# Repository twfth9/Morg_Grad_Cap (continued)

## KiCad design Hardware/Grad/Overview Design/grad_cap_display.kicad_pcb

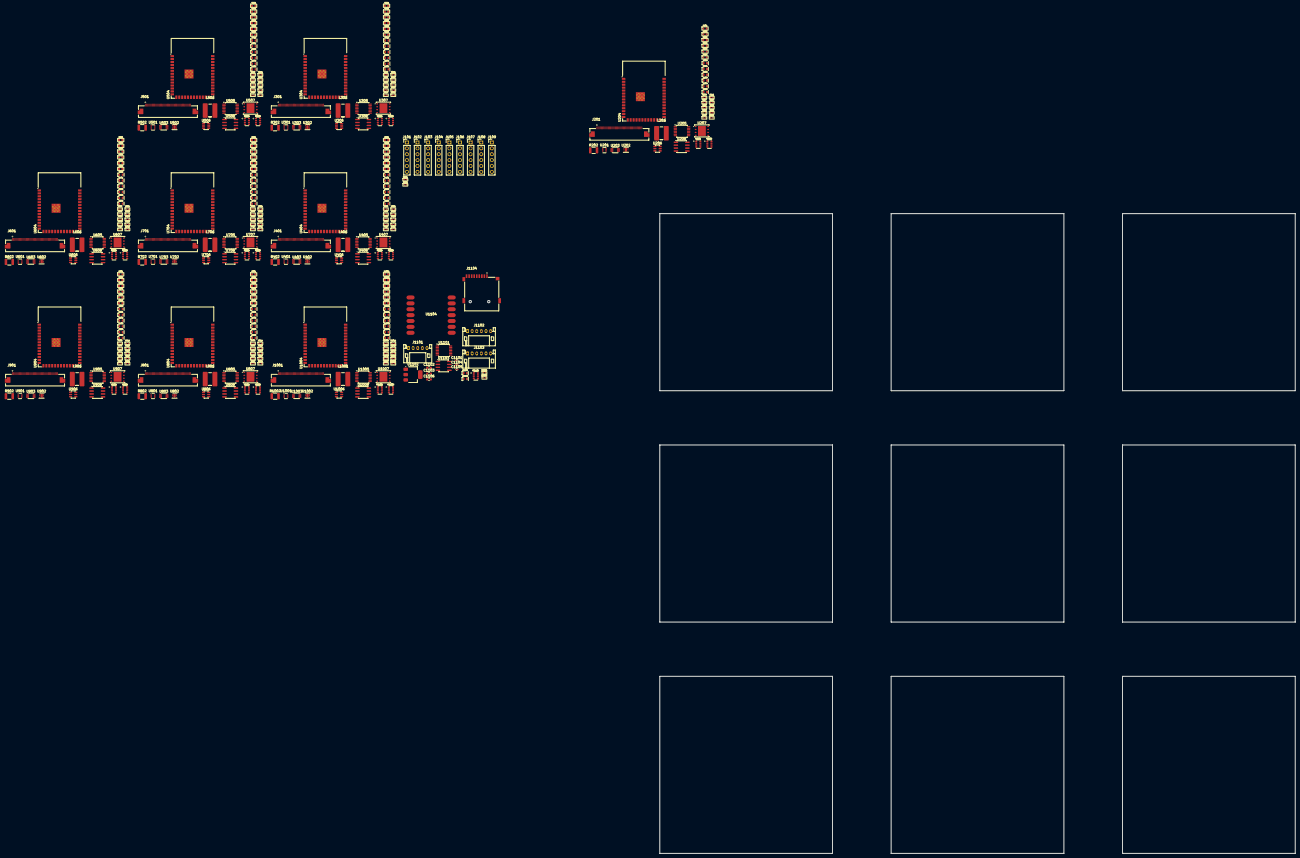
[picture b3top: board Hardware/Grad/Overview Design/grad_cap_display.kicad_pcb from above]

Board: 2 copper layers, 274.7 x 276.5 mm, 345 parts (0 on the bottom side), 444 nets, no tracks yet.

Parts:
C201, C203, C301, C303, C401, C403, C501, C503, C601, C603, C701, C703, C801, C803, C901, C903, C1001, C1003: 1uF; Worthington_C_0603
C202, C204, C206, C215, C302, C304, C306, C315, C402, C404, C406, C415, C502, C504, C506, C515, C602, C604, C606, C615, C702, C704, C706, C715, C802, C804, C806, C815, C902, C904, C906, C915, C1002, C1004, C1006, C1015: 22uF; Worthington_C_0603
C205, C207, C208, C209, C210, C211, C213, C214, C216, C305, C307, C308, C309, C310, C311, C313, C314, C316, C405, C407, C408, C409, C410, C411, C413, C414, C416, C505, C507, C508, C509, C510, C511, C513, C514, C516, C605, C607, C608, C609, C610, C611, C613, C614, C616, C705, C707, C708, C709, C710, C711, C713, C714, C716, C805, C807, C808, C809, C810, C811, C813, C814, C816, C905, C907, C908, C909, C910, C911, C913, C914, C916, C1005, C1007, C1008, C1009, C1010, C1011, C1013, C1014, C1016: 100nF; Worthington_C_0402
C212, C312, C412, C512, C612, C712, C812, C912, C1012: 22uF; Worthington_D_0603
C1101, C1104, C1105: 100nF; C_0402_1005Metric
C1102, C1103, C1106: 22uF; C_0603_1608Metric
D201, D301, D401, D501, D601, D701, D801, D901, D1001, D1101, D1102: LED_Small; Worthington_LED_0603
D202, D203, D204, D205, D302, D303, D304, D305, D402, D403, D404, D405, D502, D503, D504, D505, D602, D603, D604, D605, D702, D703, D704, D705, D802, D803, D804, D805, D902, D903, D904, D905, D1002, D1003, D1004, D1005: RED; Worthington_LED_0603
J101, J102, J103, J104, J105, J106, J107, J108, J109: 6-Pos 2.54mm Header; PinHeader_1x06_P2.54mm_Vertical
J201, J301, J401, J501, J601, J701, J801, J901, J1001: Amphenol 40-Pin FPC; AMPHENOL_62684-402100ALF
J1101: JST-PH SPI; JST_PH_S5B-PH-K_1x05_P2.00mm_Horizontal
J1102: JST-PH UART/I2C; JST_PH_S6B-PH-K_1x06_P2.00mm_Horizontal
J1103: JST-PH A#; JST_PH_S6B-PH-K_1x06_P2.00mm_Horizontal
J1104: Micro_SD_Card; CUI_MSD-4-A
L201, L301, L401, L501, L601, L701, L801, L901, L1001: 22uH; CDRH5D28
R101, R102: 120; Worthington_R_0402
R201, R301, R401, R501, R601, R701, R801, R901, R1001, R1102: 430; Worthington_R_0402
R202, R302, R402, R502, R602, R702, R802, R902, R1002: 10; R_1210_3225Metric
R1101: 1k; Worthington_R_0402
RN201, RN301, RN401, RN501, RN601, RN701, RN801, RN901, RN1001: 10k; RESCAXE80P320X160X70-8N
RN202, RN302, RN402, RN502, RN602, RN702, RN802, RN902, RN1002: 430; RESCAXE80P320X160X70-8N
RN1101: 47k; RESCAXE80P320X160X70-8N
U201, U301, U401, U501, U601, U701, U801, U901, U1001: LM66200DRLR; SOT-583-8
U202, U302, U402, U502, U602, U702, U802, U902, U1002: TLV75733PDRV; WSON-6-1EP_2x2mm_P0.65mm_EP1x1.6mm
U203, U303, U403, U503, U603, U703, U803, U903, U1003: SN74LVC1G139; VSSOP-8_2.3x2mm_P0.5mm
U204, U304, U404, U504, U604, U704, U804, U904, U1004: ESP32-S3-WROOM-1-N8R8; ESP32-S3-WROOM-1
U205, U305, U405, U505, U605, U705, U805, U905, U1005, U1101: TC7MBL3126CFT; TSSOP-14_4.4x5mm_P0.65mm
U206, U306, U406, U506, U606, U706, U806, U906, U1006: AP3019AKTTR; TSOT-23-6
U207, U307, U407, U507, U607, U707, U807, U907, U1007: W25Q128JVP; WSON-8-1EP_6x5mm_P1.27mm_EP3.4x4.3mm
U208, U308, U408, U508, U608, U708, U808, U908, U1008, U1103: THVD1400D; SOIC-8_3.9x4.9mm_P1.27mm
U1102: AZ1117-5.0; SOT-223-3_TabPin2
U1104: QTPy SAMD21; Py_QT_SAMD21

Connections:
/ESP32 1/+3V3: C204.1, C205.1, C206.1, C207.1, C208.1, C209.1, C210.1, C211.1, C216.1, D201.2 (A), J201.5 (VDD), RN201.1 (4), RN201.2, RN201.3, RN201.4, U202.1 (OUT), U203.8 (VCC), U204.2 (3V3), U205.14 (VCC), U207.8 (VCC), U208.8 (VCC)
/ESP32 1/BATT_IN: C202.1, L201.1, U201.3 (VIN1), U206.1 (SW)
/ESP32 1/LCD_RGB_DB0: J201.16 (DB0), U204.38 (IO2)
/ESP32 1/LCD_RGB_DB1: J201.17 (DB1), U204.4 (IO4)
/ESP32 1/LCD_RGB_DB2: J201.18 (DB2), U204.5 (IO5)
/ESP32 1/LCD_RGB_DB3: J201.19 (DB3), U204.6 (IO6)
/ESP32 1/LCD_RGB_DB4: J201.20 (DB4), U204.7 (IO7)
/ESP32 1/LCD_RGB_DB5: J201.21 (DB5), U204.21 (IO13)
/ESP32 1/LCD_RGB_DB6: J201.22 (DB6), U204.22 (IO14)
/ESP32 1/LCD_RGB_DB7: J201.23 (DB7), U204.8 (IO15)
/ESP32 1/LCD_RGB_DB8: J201.24 (DB8), U204.9 (IO16)
/ESP32 1/LCD_RGB_DB9: J201.25 (DB9), U204.10 (IO17)
/ESP32 1/LCD_RGB_DB10: J201.26 (DB10), U204.11 (IO18)
/ESP32 1/LCD_RGB_DB11: J201.27 (DB11), U204.13 (USB_D-)
/ESP32 1/LCD_RGB_DB12: J201.28 (DB12), U204.14 (USB_D+)
/ESP32 1/LCD_RGB_DB13: J201.29 (DB13), U204.35 (IO42)
/ESP32 1/LCD_RGB_DB14: J201.30 (DB14), U204.24 (IO47)
/ESP32 1/LCD_RGB_DB15: J201.31 (DB15), U204.25 (IO48)
/ESP32 1/LCD_RGB_DE: J201.13 (DE), U204.34 (IO41)
/ESP32 1/LCD_RGB_HSYNC: J201.15 (HS), U204.32 (IO39)
/ESP32 1/LCD_RGB_PCLK: J201.12 (PCLK), U204.31 (IO38)
/ESP32 1/LCD_RGB_VSYNC: J201.14 (VS), U204.33 (IO40)
/ESP32 1/PWR_IN: C203.1, U201.2 (VOUT), U201.7 (VOUT), U202.4 (EN), U202.6 (IN)
/ESP32 1/SPI_CS0: U203.1 (A), U204.18 (IO10)
/ESP32 1/SPI_CS1: U203.2 (B), U204.16 (IO46)
/ESP32 1/SPI_CS_FLASH: D204.2 (A), RN201.6, U203.6 (Y1), U207.1 (~CS)
/ESP32 1/SPI_CS_LCD: D205.2 (A), J201.11 (CS), RN201.5, U203.7 (Y0)
/ESP32 1/SPI_CS_µSD: D203.2 (A), D303.2 (A), D403.2 (A), D503.2 (A), D603.2 (A), D703.2 (A), D803.2 (A), D903.2 (A), D1003.2 (A), J1103.3, J1104.2 (DAT3/CD), RN201.7 (5), RN301.7 (5), RN401.7 (5), RN501.7 (5), RN601.7 (5), RN701.7 (5), RN801.7 (5), RN901.7 (5), RN1001.7 (5), RN1101.5, U203.5 (Y2), U205.11 (B4), U205.12 (A4), U303.5 (Y2), U305.11 (B4), U305.12 (A4), U403.5 (Y2), U405.11 (B4), U405.12 (A4), U503.5 (Y2), U505.11 (B4), U505.12 (A4), U603.5 (Y2), U605.11 (B4), U605.12 (A4), U703.5 (Y2), U705.11 (B4), U705.12 (A4), U803.5 (Y2), U805.11 (B4), U805.12 (A4), U903.5 (Y2), U905.11 (B4), U905.12 (A4), U1003.5 (Y2), U1005.11 (B4), U1005.12 (A4), U1101.11 (B4), U1101.12 (A4), U1104.2 (A1)
/ESP32 1/SPI_MISO: U204.26 (IO45), U205.3 (B1), U207.2 (DO/IO_{1})
/ESP32 1/SPI_MOSI: J201.9 (SDA), U204.12 (IO8), U205.5 (A2), U207.5 (DI/IO_{0})
/ESP32 1/SPI_SCK: J201.10 (SCK), U204.17 (IO9), U205.9 (A3), U207.6 (CLK)
/ESP32 1/SPI_µSD_BUS_CONNECT: D202.2 (A), RN201.8, U203.3 (Y3), U205.1 (1~OE), U205.4 (2~OE), U205.10 (3~OE), U205.13 (4~OE)
/ESP32 1/UART-RS485_RX: U204.20 (IO12), U208.1 (RO)
/ESP32 1/UART-RS485_TX: U204.19 (IO11), U208.4 (DI)
/ESP32 1/UART_RS485_DE: U204.23 (IO21), U208.2 (~RE), U208.3 (DE)
/ESP32 2/+3V3: C304.1, C305.1, C306.1, C307.1, C308.1, C309.1, C310.1, C311.1, C316.1, D301.2 (A), J301.5 (VDD), RN301.1 (4), RN301.2, RN301.3, RN301.4, U302.1 (OUT), U303.8 (VCC), U304.2 (3V3), U305.14 (VCC), U307.8 (VCC), U308.8 (VCC)
/ESP32 2/BATT_IN: C302.1, L301.1, U301.3 (VIN1), U306.1 (SW)
/ESP32 2/LCD_RGB_DB0: J301.16 (DB0), U304.38 (IO2)
/ESP32 2/LCD_RGB_DB1: J301.17 (DB1), U304.4 (IO4)
/ESP32 2/LCD_RGB_DB2: J301.18 (DB2), U304.5 (IO5)
/ESP32 2/LCD_RGB_DB3: J301.19 (DB3), U304.6 (IO6)
/ESP32 2/LCD_RGB_DB4: J301.20 (DB4), U304.7 (IO7)
/ESP32 2/LCD_RGB_DB5: J301.21 (DB5), U304.21 (IO13)
/ESP32 2/LCD_RGB_DB6: J301.22 (DB6), U304.22 (IO14)
/ESP32 2/LCD_RGB_DB7: J301.23 (DB7), U304.8 (IO15)
/ESP32 2/LCD_RGB_DB8: J301.24 (DB8), U304.9 (IO16)
/ESP32 2/LCD_RGB_DB9: J301.25 (DB9), U304.10 (IO17)
/ESP32 2/LCD_RGB_DB10: J301.26 (DB10), U304.11 (IO18)
/ESP32 2/LCD_RGB_DB11: J301.27 (DB11), U304.13 (USB_D-)
/ESP32 2/LCD_RGB_DB12: J301.28 (DB12), U304.14 (USB_D+)
/ESP32 2/LCD_RGB_DB13: J301.29 (DB13), U304.35 (IO42)
/ESP32 2/LCD_RGB_DB14: J301.30 (DB14), U304.24 (IO47)
/ESP32 2/LCD_RGB_DB15: J301.31 (DB15), U304.25 (IO48)
/ESP32 2/LCD_RGB_DE: J301.13 (DE), U304.34 (IO41)
/ESP32 2/LCD_RGB_HSYNC: J301.15 (HS), U304.32 (IO39)
/ESP32 2/LCD_RGB_PCLK: J301.12 (PCLK), U304.31 (IO38)
/ESP32 2/LCD_RGB_VSYNC: J301.14 (VS), U304.33 (IO40)
/ESP32 2/PWR_IN: C303.1, U301.2 (VOUT), U301.7 (VOUT), U302.4 (EN), U302.6 (IN)
/ESP32 2/SPI_CS0: U303.1 (A), U304.18 (IO10)
/ESP32 2/SPI_CS1: U303.2 (B), U304.16 (IO46)
/ESP32 2/SPI_CS_FLASH: D304.2 (A), RN301.6, U303.6 (Y1), U307.1 (~CS)
/ESP32 2/SPI_CS_LCD: D305.2 (A), J301.11 (CS), RN301.5, U303.7 (Y0)
/ESP32 2/SPI_MISO: U304.26 (IO45), U305.3 (B1), U307.2 (DO/IO_{1})
/ESP32 2/SPI_MOSI: J301.9 (SDA), U304.12 (IO8), U305.5 (A2), U307.5 (DI/IO_{0})
/ESP32 2/SPI_SCK: J301.10 (SCK), U304.17 (IO9), U305.9 (A3), U307.6 (CLK)
/ESP32 2/SPI_µSD_BUS_CONNECT: D302.2 (A), RN301.8, U303.3 (Y3), U305.1 (1~OE), U305.4 (2~OE), U305.10 (3~OE), U305.13 (4~OE)
/ESP32 2/UART-RS485_RX: U304.20 (IO12), U308.1 (RO)
/ESP32 2/UART-RS485_TX: U304.19 (IO11), U308.4 (DI)
/ESP32 2/UART_RS485_DE: U304.23 (IO21), U308.2 (~RE), U308.3 (DE)
/ESP32 3/+3V3: C404.1, C405.1, C406.1, C407.1, C408.1, C409.1, C410.1, C411.1, C416.1, D401.2 (A), J401.5 (VDD), RN401.1 (4), RN401.2, RN401.3, RN401.4, U402.1 (OUT), U403.8 (VCC), U404.2 (3V3), U405.14 (VCC), U407.8 (VCC), U408.8 (VCC)
/ESP32 3/BATT_IN: C402.1, L401.1, U401.3 (VIN1), U406.1 (SW)
/ESP32 3/LCD_RGB_DB0: J401.16 (DB0), U404.38 (IO2)
/ESP32 3/LCD_RGB_DB1: J401.17 (DB1), U404.4 (IO4)
/ESP32 3/LCD_RGB_DB2: J401.18 (DB2), U404.5 (IO5)
/ESP32 3/LCD_RGB_DB3: J401.19 (DB3), U404.6 (IO6)
/ESP32 3/LCD_RGB_DB4: J401.20 (DB4), U404.7 (IO7)
/ESP32 3/LCD_RGB_DB5: J401.21 (DB5), U404.21 (IO13)
/ESP32 3/LCD_RGB_DB6: J401.22 (DB6), U404.22 (IO14)
/ESP32 3/LCD_RGB_DB7: J401.23 (DB7), U404.8 (IO15)
/ESP32 3/LCD_RGB_DB8: J401.24 (DB8), U404.9 (IO16)
/ESP32 3/LCD_RGB_DB9: J401.25 (DB9), U404.10 (IO17)
/ESP32 3/LCD_RGB_DB10: J401.26 (DB10), U404.11 (IO18)
/ESP32 3/LCD_RGB_DB11: J401.27 (DB11), U404.13 (USB_D-)
/ESP32 3/LCD_RGB_DB12: J401.28 (DB12), U404.14 (USB_D+)
/ESP32 3/LCD_RGB_DB13: J401.29 (DB13), U404.35 (IO42)
/ESP32 3/LCD_RGB_DB14: J401.30 (DB14), U404.24 (IO47)
/ESP32 3/LCD_RGB_DB15: J401.31 (DB15), U404.25 (IO48)
/ESP32 3/LCD_RGB_DE: J401.13 (DE), U404.34 (IO41)
/ESP32 3/LCD_RGB_HSYNC: J401.15 (HS), U404.32 (IO39)
/ESP32 3/LCD_RGB_PCLK: J401.12 (PCLK), U404.31 (IO38)
/ESP32 3/LCD_RGB_VSYNC: J401.14 (VS), U404.33 (IO40)
/ESP32 3/PWR_IN: C403.1, U401.2 (VOUT), U401.7 (VOUT), U402.4 (EN), U402.6 (IN)
/ESP32 3/SPI_CS0: U403.1 (A), U404.18 (IO10)
/ESP32 3/SPI_CS1: U403.2 (B), U404.16 (IO46)
/ESP32 3/SPI_CS_FLASH: D404.2 (A), RN401.6, U403.6 (Y1), U407.1 (~CS)
/ESP32 3/SPI_CS_LCD: D405.2 (A), J401.11 (CS), RN401.5, U403.7 (Y0)
/ESP32 3/SPI_MISO: U404.26 (IO45), U405.3 (B1), U407.2 (DO/IO_{1})
/ESP32 3/SPI_MOSI: J401.9 (SDA), U404.12 (IO8), U405.5 (A2), U407.5 (DI/IO_{0})
/ESP32 3/SPI_SCK: J401.10 (SCK), U404.17 (IO9), U405.9 (A3), U407.6 (CLK)
/ESP32 3/SPI_µSD_BUS_CONNECT: D402.2 (A), RN401.8, U403.3 (Y3), U405.1 (1~OE), U405.4 (2~OE), U405.10 (3~OE), U405.13 (4~OE)
/ESP32 3/UART-RS485_RX: U404.20 (IO12), U408.1 (RO)
/ESP32 3/UART-RS485_TX: U404.19 (IO11), U408.4 (DI)
/ESP32 3/UART_RS485_DE: U404.23 (IO21), U408.2 (~RE), U408.3 (DE)
/ESP32 4/+3V3: C504.1, C505.1, C506.1, C507.1, C508.1, C509.1, C510.1, C511.1, C516.1, D501.2 (A), J501.5 (VDD), RN501.1 (4), RN501.2, RN501.3, RN501.4, U502.1 (OUT), U503.8 (VCC), U504.2 (3V3), U505.14 (VCC), U507.8 (VCC), U508.8 (VCC)
/ESP32 4/BATT_IN: C502.1, L501.1, U501.3 (VIN1), U506.1 (SW)
/ESP32 4/LCD_RGB_DB0: J501.16 (DB0), U504.38 (IO2)
/ESP32 4/LCD_RGB_DB1: J501.17 (DB1), U504.4 (IO4)
/ESP32 4/LCD_RGB_DB2: J501.18 (DB2), U504.5 (IO5)
/ESP32 4/LCD_RGB_DB3: J501.19 (DB3), U504.6 (IO6)
/ESP32 4/LCD_RGB_DB4: J501.20 (DB4), U504.7 (IO7)
/ESP32 4/LCD_RGB_DB5: J501.21 (DB5), U504.21 (IO13)
/ESP32 4/LCD_RGB_DB6: J501.22 (DB6), U504.22 (IO14)
/ESP32 4/LCD_RGB_DB7: J501.23 (DB7), U504.8 (IO15)
/ESP32 4/LCD_RGB_DB8: J501.24 (DB8), U504.9 (IO16)
/ESP32 4/LCD_RGB_DB9: J501.25 (DB9), U504.10 (IO17)
/ESP32 4/LCD_RGB_DB10: J501.26 (DB10), U504.11 (IO18)
/ESP32 4/LCD_RGB_DB11: J501.27 (DB11), U504.13 (USB_D-)
/ESP32 4/LCD_RGB_DB12: J501.28 (DB12), U504.14 (USB_D+)
/ESP32 4/LCD_RGB_DB13: J501.29 (DB13), U504.35 (IO42)
/ESP32 4/LCD_RGB_DB14: J501.30 (DB14), U504.24 (IO47)
/ESP32 4/LCD_RGB_DB15: J501.31 (DB15), U504.25 (IO48)
/ESP32 4/LCD_RGB_DE: J501.13 (DE), U504.34 (IO41)
/ESP32 4/LCD_RGB_HSYNC: J501.15 (HS), U504.32 (IO39)
/ESP32 4/LCD_RGB_PCLK: J501.12 (PCLK), U504.31 (IO38)
/ESP32 4/LCD_RGB_VSYNC: J501.14 (VS), U504.33 (IO40)
/ESP32 4/PWR_IN: C503.1, U501.2 (VOUT), U501.7 (VOUT), U502.4 (EN), U502.6 (IN)
/ESP32 4/SPI_CS0: U503.1 (A), U504.18 (IO10)
/ESP32 4/SPI_CS1: U503.2 (B), U504.16 (IO46)
/ESP32 4/SPI_CS_FLASH: D504.2 (A), RN501.6, U503.6 (Y1), U507.1 (~CS)
/ESP32 4/SPI_CS_LCD: D505.2 (A), J501.11 (CS), RN501.5, U503.7 (Y0)
/ESP32 4/SPI_MISO: U504.26 (IO45), U505.3 (B1), U507.2 (DO/IO_{1})
/ESP32 4/SPI_MOSI: J501.9 (SDA), U504.12 (IO8), U505.5 (A2), U507.5 (DI/IO_{0})
/ESP32 4/SPI_SCK: J501.10 (SCK), U504.17 (IO9), U505.9 (A3), U507.6 (CLK)
/ESP32 4/SPI_µSD_BUS_CONNECT: D502.2 (A), RN501.8, U503.3 (Y3), U505.1 (1~OE), U505.4 (2~OE), U505.10 (3~OE), U505.13 (4~OE)
/ESP32 4/UART-RS485_RX: U504.20 (IO12), U508.1 (RO)
/ESP32 4/UART-RS485_TX: U504.19 (IO11), U508.4 (DI)
/ESP32 4/UART_RS485_DE: U504.23 (IO21), U508.2 (~RE), U508.3 (DE)
/ESP32 5/+3V3: C604.1, C605.1, C606.1, C607.1, C608.1, C609.1, C610.1, C611.1, C616.1, D601.2 (A), J601.5 (VDD), RN601.1 (4), RN601.2, RN601.3, RN601.4, U602.1 (OUT), U603.8 (VCC), U604.2 (3V3), U605.14 (VCC), U607.8 (VCC), U608.8 (VCC)
/ESP32 5/BATT_IN: C602.1, L601.1, U601.3 (VIN1), U606.1 (SW)
/ESP32 5/LCD_RGB_DB0: J601.16 (DB0), U604.38 (IO2)
/ESP32 5/LCD_RGB_DB1: J601.17 (DB1), U604.4 (IO4)
/ESP32 5/LCD_RGB_DB2: J601.18 (DB2), U604.5 (IO5)
/ESP32 5/LCD_RGB_DB3: J601.19 (DB3), U604.6 (IO6)
/ESP32 5/LCD_RGB_DB4: J601.20 (DB4), U604.7 (IO7)
/ESP32 5/LCD_RGB_DB5: J601.21 (DB5), U604.21 (IO13)
/ESP32 5/LCD_RGB_DB6: J601.22 (DB6), U604.22 (IO14)
/ESP32 5/LCD_RGB_DB7: J601.23 (DB7), U604.8 (IO15)
/ESP32 5/LCD_RGB_DB8: J601.24 (DB8), U604.9 (IO16)
/ESP32 5/LCD_RGB_DB9: J601.25 (DB9), U604.10 (IO17)
/ESP32 5/LCD_RGB_DB10: J601.26 (DB10), U604.11 (IO18)
/ESP32 5/LCD_RGB_DB11: J601.27 (DB11), U604.13 (USB_D-)
/ESP32 5/LCD_RGB_DB12: J601.28 (DB12), U604.14 (USB_D+)
/ESP32 5/LCD_RGB_DB13: J601.29 (DB13), U604.35 (IO42)
/ESP32 5/LCD_RGB_DB14: J601.30 (DB14), U604.24 (IO47)
/ESP32 5/LCD_RGB_DB15: J601.31 (DB15), U604.25 (IO48)
/ESP32 5/LCD_RGB_DE: J601.13 (DE), U604.34 (IO41)
/ESP32 5/LCD_RGB_HSYNC: J601.15 (HS), U604.32 (IO39)
/ESP32 5/LCD_RGB_PCLK: J601.12 (PCLK), U604.31 (IO38)
/ESP32 5/LCD_RGB_VSYNC: J601.14 (VS), U604.33 (IO40)
/ESP32 5/PWR_IN: C603.1, U601.2 (VOUT), U601.7 (VOUT), U602.4 (EN), U602.6 (IN)
/ESP32 5/SPI_CS0: U603.1 (A), U604.18 (IO10)
/ESP32 5/SPI_CS1: U603.2 (B), U604.16 (IO46)
/ESP32 5/SPI_CS_FLASH: D604.2 (A), RN601.6, U603.6 (Y1), U607.1 (~CS)
/ESP32 5/SPI_CS_LCD: D605.2 (A), J601.11 (CS), RN601.5, U603.7 (Y0)
/ESP32 5/SPI_MISO: U604.26 (IO45), U605.3 (B1), U607.2 (DO/IO_{1})
/ESP32 5/SPI_MOSI: J601.9 (SDA), U604.12 (IO8), U605.5 (A2), U607.5 (DI/IO_{0})
/ESP32 5/SPI_SCK: J601.10 (SCK), U604.17 (IO9), U605.9 (A3), U607.6 (CLK)
/ESP32 5/SPI_µSD_BUS_CONNECT: D602.2 (A), RN601.8, U603.3 (Y3), U605.1 (1~OE), U605.4 (2~OE), U605.10 (3~OE), U605.13 (4~OE)
/ESP32 5/UART-RS485_RX: U604.20 (IO12), U608.1 (RO)
/ESP32 5/UART-RS485_TX: U604.19 (IO11), U608.4 (DI)
/ESP32 5/UART_RS485_DE: U604.23 (IO21), U608.2 (~RE), U608.3 (DE)
/ESP32 6/+3V3: C704.1, C705.1, C706.1, C707.1, C708.1, C709.1, C710.1, C711.1, C716.1, D701.2 (A), J701.5 (VDD), RN701.1 (4), RN701.2, RN701.3, RN701.4, U702.1 (OUT), U703.8 (VCC), U704.2 (3V3), U705.14 (VCC), U707.8 (VCC), U708.8 (VCC)
/ESP32 6/BATT_IN: C702.1, L701.1, U701.3 (VIN1), U706.1 (SW)
/ESP32 6/LCD_RGB_DB0: J701.16 (DB0), U704.38 (IO2)
/ESP32 6/LCD_RGB_DB1: J701.17 (DB1), U704.4 (IO4)
/ESP32 6/LCD_RGB_DB2: J701.18 (DB2), U704.5 (IO5)
/ESP32 6/LCD_RGB_DB3: J701.19 (DB3), U704.6 (IO6)
/ESP32 6/LCD_RGB_DB4: J701.20 (DB4), U704.7 (IO7)
/ESP32 6/LCD_RGB_DB5: J701.21 (DB5), U704.21 (IO13)
/ESP32 6/LCD_RGB_DB6: J701.22 (DB6), U704.22 (IO14)
/ESP32 6/LCD_RGB_DB7: J701.23 (DB7), U704.8 (IO15)
/ESP32 6/LCD_RGB_DB8: J701.24 (DB8), U704.9 (IO16)
/ESP32 6/LCD_RGB_DB9: J701.25 (DB9), U704.10 (IO17)
/ESP32 6/LCD_RGB_DB10: J701.26 (DB10), U704.11 (IO18)
/ESP32 6/LCD_RGB_DB11: J701.27 (DB11), U704.13 (USB_D-)
/ESP32 6/LCD_RGB_DB12: J701.28 (DB12), U704.14 (USB_D+)
/ESP32 6/LCD_RGB_DB13: J701.29 (DB13), U704.35 (IO42)
/ESP32 6/LCD_RGB_DB14: J701.30 (DB14), U704.24 (IO47)
/ESP32 6/LCD_RGB_DB15: J701.31 (DB15), U704.25 (IO48)
/ESP32 6/LCD_RGB_DE: J701.13 (DE), U704.34 (IO41)
/ESP32 6/LCD_RGB_HSYNC: J701.15 (HS), U704.32 (IO39)
/ESP32 6/LCD_RGB_PCLK: J701.12 (PCLK), U704.31 (IO38)
/ESP32 6/LCD_RGB_VSYNC: J701.14 (VS), U704.33 (IO40)
/ESP32 6/PWR_IN: C703.1, U701.2 (VOUT), U701.7 (VOUT), U702.4 (EN), U702.6 (IN)
/ESP32 6/SPI_CS0: U703.1 (A), U704.18 (IO10)
/ESP32 6/SPI_CS1: U703.2 (B), U704.16 (IO46)
/ESP32 6/SPI_CS_FLASH: D704.2 (A), RN701.6, U703.6 (Y1), U707.1 (~CS)
/ESP32 6/SPI_CS_LCD: D705.2 (A), J701.11 (CS), RN701.5, U703.7 (Y0)
/ESP32 6/SPI_MISO: U704.26 (IO45), U705.3 (B1), U707.2 (DO/IO_{1})
/ESP32 6/SPI_MOSI: J701.9 (SDA), U704.12 (IO8), U705.5 (A2), U707.5 (DI/IO_{0})
/ESP32 6/SPI_SCK: J701.10 (SCK), U704.17 (IO9), U705.9 (A3), U707.6 (CLK)
/ESP32 6/SPI_µSD_BUS_CONNECT: D702.2 (A), RN701.8, U703.3 (Y3), U705.1 (1~OE), U705.4 (2~OE), U705.10 (3~OE), U705.13 (4~OE)
/ESP32 6/UART-RS485_RX: U704.20 (IO12), U708.1 (RO)
/ESP32 6/UART-RS485_TX: U704.19 (IO11), U708.4 (DI)
/ESP32 6/UART_RS485_DE: U704.23 (IO21), U708.2 (~RE), U708.3 (DE)
/ESP32 7/+3V3: C804.1, C805.1, C806.1, C807.1, C808.1, C809.1, C810.1, C811.1, C816.1, D801.2 (A), J801.5 (VDD), RN801.1 (4), RN801.2, RN801.3, RN801.4, U802.1 (OUT), U803.8 (VCC), U804.2 (3V3), U805.14 (VCC), U807.8 (VCC), U808.8 (VCC)
/ESP32 7/BATT_IN: C802.1, L801.1, U801.3 (VIN1), U806.1 (SW)
/ESP32 7/LCD_RGB_DB0: J801.16 (DB0), U804.38 (IO2)
/ESP32 7/LCD_RGB_DB1: J801.17 (DB1), U804.4 (IO4)
/ESP32 7/LCD_RGB_DB2: J801.18 (DB2), U804.5 (IO5)
/ESP32 7/LCD_RGB_DB3: J801.19 (DB3), U804.6 (IO6)
/ESP32 7/LCD_RGB_DB4: J801.20 (DB4), U804.7 (IO7)
/ESP32 7/LCD_RGB_DB5: J801.21 (DB5), U804.21 (IO13)
/ESP32 7/LCD_RGB_DB6: J801.22 (DB6), U804.22 (IO14)
/ESP32 7/LCD_RGB_DB7: J801.23 (DB7), U804.8 (IO15)
/ESP32 7/LCD_RGB_DB8: J801.24 (DB8), U804.9 (IO16)
/ESP32 7/LCD_RGB_DB9: J801.25 (DB9), U804.10 (IO17)
/ESP32 7/LCD_RGB_DB10: J801.26 (DB10), U804.11 (IO18)
/ESP32 7/LCD_RGB_DB11: J801.27 (DB11), U804.13 (USB_D-)
/ESP32 7/LCD_RGB_DB12: J801.28 (DB12), U804.14 (USB_D+)
/ESP32 7/LCD_RGB_DB13: J801.29 (DB13), U804.35 (IO42)
/ESP32 7/LCD_RGB_DB14: J801.30 (DB14), U804.24 (IO47)
/ESP32 7/LCD_RGB_DB15: J801.31 (DB15), U804.25 (IO48)
/ESP32 7/LCD_RGB_DE: J801.13 (DE), U804.34 (IO41)
/ESP32 7/LCD_RGB_HSYNC: J801.15 (HS), U804.32 (IO39)
/ESP32 7/LCD_RGB_PCLK: J801.12 (PCLK), U804.31 (IO38)
/ESP32 7/LCD_RGB_VSYNC: J801.14 (VS), U804.33 (IO40)
/ESP32 7/PWR_IN: C803.1, U801.2 (VOUT), U801.7 (VOUT), U802.4 (EN), U802.6 (IN)
/ESP32 7/SPI_CS0: U803.1 (A), U804.18 (IO10)
/ESP32 7/SPI_CS1: U803.2 (B), U804.16 (IO46)
/ESP32 7/SPI_CS_FLASH: D804.2 (A), RN801.6, U803.6 (Y1), U807.1 (~CS)
/ESP32 7/SPI_CS_LCD: D805.2 (A), J801.11 (CS), RN801.5, U803.7 (Y0)
/ESP32 7/SPI_MISO: U804.26 (IO45), U805.3 (B1), U807.2 (DO/IO_{1})
/ESP32 7/SPI_MOSI: J801.9 (SDA), U804.12 (IO8), U805.5 (A2), U807.5 (DI/IO_{0})
/ESP32 7/SPI_SCK: J801.10 (SCK), U804.17 (IO9), U805.9 (A3), U807.6 (CLK)
/ESP32 7/SPI_µSD_BUS_CONNECT: D802.2 (A), RN801.8, U803.3 (Y3), U805.1 (1~OE), U805.4 (2~OE), U805.10 (3~OE), U805.13 (4~OE)
/ESP32 7/UART-RS485_RX: U804.20 (IO12), U808.1 (RO)
/ESP32 7/UART-RS485_TX: U804.19 (IO11), U808.4 (DI)
/ESP32 7/UART_RS485_DE: U804.23 (IO21), U808.2 (~RE), U808.3 (DE)
/ESP32 8/+3V3: C904.1, C905.1, C906.1, C907.1, C908.1, C909.1, C910.1, C911.1, C916.1, D901.2 (A), J901.5 (VDD), RN901.1 (4), RN901.2, RN901.3, RN901.4, U902.1 (OUT), U903.8 (VCC), U904.2 (3V3), U905.14 (VCC), U907.8 (VCC), U908.8 (VCC)
/ESP32 8/BATT_IN: C902.1, L901.1, U901.3 (VIN1), U906.1 (SW)
/ESP32 8/LCD_RGB_DB0: J901.16 (DB0), U904.38 (IO2)
/ESP32 8/LCD_RGB_DB1: J901.17 (DB1), U904.4 (IO4)
/ESP32 8/LCD_RGB_DB2: J901.18 (DB2), U904.5 (IO5)
/ESP32 8/LCD_RGB_DB3: J901.19 (DB3), U904.6 (IO6)
/ESP32 8/LCD_RGB_DB4: J901.20 (DB4), U904.7 (IO7)
/ESP32 8/LCD_RGB_DB5: J901.21 (DB5), U904.21 (IO13)
/ESP32 8/LCD_RGB_DB6: J901.22 (DB6), U904.22 (IO14)
/ESP32 8/LCD_RGB_DB7: J901.23 (DB7), U904.8 (IO15)
/ESP32 8/LCD_RGB_DB8: J901.24 (DB8), U904.9 (IO16)
/ESP32 8/LCD_RGB_DB9: J901.25 (DB9), U904.10 (IO17)
/ESP32 8/LCD_RGB_DB10: J901.26 (DB10), U904.11 (IO18)
/ESP32 8/LCD_RGB_DB11: J901.27 (DB11), U904.13 (USB_D-)
/ESP32 8/LCD_RGB_DB12: J901.28 (DB12), U904.14 (USB_D+)
/ESP32 8/LCD_RGB_DB13: J901.29 (DB13), U904.35 (IO42)
/ESP32 8/LCD_RGB_DB14: J901.30 (DB14), U904.24 (IO47)
/ESP32 8/LCD_RGB_DB15: J901.31 (DB15), U904.25 (IO48)
/ESP32 8/LCD_RGB_DE: J901.13 (DE), U904.34 (IO41)
/ESP32 8/LCD_RGB_HSYNC: J901.15 (HS), U904.32 (IO39)
/ESP32 8/LCD_RGB_PCLK: J901.12 (PCLK), U904.31 (IO38)
/ESP32 8/LCD_RGB_VSYNC: J901.14 (VS), U904.33 (IO40)
/ESP32 8/PWR_IN: C903.1, U901.2 (VOUT), U901.7 (VOUT), U902.4 (EN), U902.6 (IN)
/ESP32 8/SPI_CS0: U903.1 (A), U904.18 (IO10)
/ESP32 8/SPI_CS1: U903.2 (B), U904.16 (IO46)
/ESP32 8/SPI_CS_FLASH: D904.2 (A), RN901.6, U903.6 (Y1), U907.1 (~CS)
/ESP32 8/SPI_CS_LCD: D905.2 (A), J901.11 (CS), RN901.5, U903.7 (Y0)
/ESP32 8/SPI_MISO: U904.26 (IO45), U905.3 (B1), U907.2 (DO/IO_{1})
/ESP32 8/SPI_MOSI: J901.9 (SDA), U904.12 (IO8), U905.5 (A2), U907.5 (DI/IO_{0})
/ESP32 8/SPI_SCK: J901.10 (SCK), U904.17 (IO9), U905.9 (A3), U907.6 (CLK)
/ESP32 8/SPI_µSD_BUS_CONNECT: D902.2 (A), RN901.8, U903.3 (Y3), U905.1 (1~OE), U905.4 (2~OE), U905.10 (3~OE), U905.13 (4~OE)
/ESP32 8/UART-RS485_RX: U904.20 (IO12), U908.1 (RO)
/ESP32 8/UART-RS485_TX: U904.19 (IO11), U908.4 (DI)
/ESP32 8/UART_RS485_DE: U904.23 (IO21), U908.2 (~RE), U908.3 (DE)
/ESP32 9/+3V3: C1004.1, C1005.1, C1006.1, C1007.1, C1008.1, C1009.1, C1010.1, C1011.1, C1016.1, D1001.2 (A), J1001.5 (VDD), RN1001.1 (4), RN1001.2, RN1001.3, RN1001.4, U1002.1 (OUT), U1003.8 (VCC), U1004.2 (3V3), U1005.14 (VCC), U1007.8 (VCC), U1008.8 (VCC)
/ESP32 9/BATT_IN: C1002.1, L1001.1, U1001.3 (VIN1), U1006.1 (SW)
/ESP32 9/LCD_RGB_DB0: J1001.16 (DB0), U1004.38 (IO2)
/ESP32 9/LCD_RGB_DB1: J1001.17 (DB1), U1004.4 (IO4)
/ESP32 9/LCD_RGB_DB2: J1001.18 (DB2), U1004.5 (IO5)
/ESP32 9/LCD_RGB_DB3: J1001.19 (DB3), U1004.6 (IO6)
/ESP32 9/LCD_RGB_DB4: J1001.20 (DB4), U1004.7 (IO7)
/ESP32 9/LCD_RGB_DB5: J1001.21 (DB5), U1004.21 (IO13)
/ESP32 9/LCD_RGB_DB6: J1001.22 (DB6), U1004.22 (IO14)
/ESP32 9/LCD_RGB_DB7: J1001.23 (DB7), U1004.8 (IO15)
/ESP32 9/LCD_RGB_DB8: J1001.24 (DB8), U1004.9 (IO16)
/ESP32 9/LCD_RGB_DB9: J1001.25 (DB9), U1004.10 (IO17)
/ESP32 9/LCD_RGB_DB10: J1001.26 (DB10), U1004.11 (IO18)
/ESP32 9/LCD_RGB_DB11: J1001.27 (DB11), U1004.13 (USB_D-)
/ESP32 9/LCD_RGB_DB12: J1001.28 (DB12), U1004.14 (USB_D+)
/ESP32 9/LCD_RGB_DB13: J1001.29 (DB13), U1004.35 (IO42)
/ESP32 9/LCD_RGB_DB14: J1001.30 (DB14), U1004.24 (IO47)
/ESP32 9/LCD_RGB_DB15: J1001.31 (DB15), U1004.25 (IO48)
/ESP32 9/LCD_RGB_DE: J1001.13 (DE), U1004.34 (IO41)
/ESP32 9/LCD_RGB_HSYNC: J1001.15 (HS), U1004.32 (IO39)
/ESP32 9/LCD_RGB_PCLK: J1001.12 (PCLK), U1004.31 (IO38)
/ESP32 9/LCD_RGB_VSYNC: J1001.14 (VS), U1004.33 (IO40)
/ESP32 9/PWR_IN: C1003.1, U1001.2 (VOUT), U1001.7 (VOUT), U1002.4 (EN), U1002.6 (IN)
/ESP32 9/SPI_CS0: U1003.1 (A), U1004.18 (IO10)
/ESP32 9/SPI_CS1: U1003.2 (B), U1004.16 (IO46)
/ESP32 9/SPI_CS_FLASH: D1004.2 (A), RN1001.6, U1003.6 (Y1), U1007.1 (~CS)
/ESP32 9/SPI_CS_LCD: D1005.2 (A), J1001.11 (CS), RN1001.5, U1003.7 (Y0)
/ESP32 9/SPI_MISO: U1004.26 (IO45), U1005.3 (B1), U1007.2 (DO/IO_{1})
/ESP32 9/SPI_MOSI: J1001.9 (SDA), U1004.12 (IO8), U1005.5 (A2), U1007.5 (DI/IO_{0})
/ESP32 9/SPI_SCK: J1001.10 (SCK), U1004.17 (IO9), U1005.9 (A3), U1007.6 (CLK)
/ESP32 9/SPI_µSD_BUS_CONNECT: D1002.2 (A), RN1001.8, U1003.3 (Y3), U1005.1 (1~OE), U1005.4 (2~OE), U1005.10 (3~OE), U1005.13 (4~OE)
/ESP32 9/UART-RS485_RX: U1004.20 (IO12), U1008.1 (RO)
/ESP32 9/UART-RS485_TX: U1004.19 (IO11), U1008.4 (DI)
/ESP32 9/UART_RS485_DE: U1004.23 (IO21), U1008.2 (~RE), U1008.3 (DE)
/FRAME_SYNC: J1103.4, R101.1, R102.2, U204.39 (IO1), U208.7 (B), U304.39 (IO1), U308.7 (B), U404.39 (IO1), U408.7 (B), U504.39 (IO1), U508.7 (B), U604.39 (IO1), U608.7 (B), U704.39 (IO1), U708.7 (B), U804.39 (IO1), U808.7 (B), U904.39 (IO1), U908.7 (B), U1004.39 (IO1), U1008.7 (B), U1103.7 (B), U1104.3 (A2)
/PROG_ESP1_EN: J101.2, U204.3 (EN)
/PROG_ESP1_IO0: J101.3, U204.27 (IO0)
/PROG_ESP1_PWR: C201.1, J101.1, U201.6 (VIN2)
/PROG_ESP1_RXD0: J101.5, U204.36 (RXD0)
/PROG_ESP1_TXD0: J101.4, U204.37 (TXD0)
/PROG_ESP2_EN: J102.2, U304.3 (EN)
/PROG_ESP2_IO0: J102.3, U304.27 (IO0)
/PROG_ESP2_PWR: C301.1, J102.1, U301.6 (VIN2)
/PROG_ESP2_RXD0: J102.5, U304.36 (RXD0)
/PROG_ESP2_TXD0: J102.4, U304.37 (TXD0)
/PROG_ESP3_EN: J103.2, U404.3 (EN)
/PROG_ESP3_IO0: J103.3, U404.27 (IO0)
/PROG_ESP3_PWR: C401.1, J103.1, U401.6 (VIN2)
/PROG_ESP3_RXD0: J103.5, U404.36 (RXD0)
/PROG_ESP3_TXD0: J103.4, U404.37 (TXD0)
/PROG_ESP4_EN: J104.2, U504.3 (EN)
/PROG_ESP4_IO0: J104.3, U504.27 (IO0)
/PROG_ESP4_PWR: C501.1, J104.1, U501.6 (VIN2)
/PROG_ESP4_RXD0: J104.5, U504.36 (RXD0)
/PROG_ESP4_TXD0: J104.4, U504.37 (TXD0)
/PROG_ESP5_EN: J105.2, U604.3 (EN)
/PROG_ESP5_IO0: J105.3, U604.27 (IO0)
/PROG_ESP5_PWR: C601.1, J105.1, U601.6 (VIN2)
/PROG_ESP5_RXD0: J105.5, U604.36 (RXD0)
/PROG_ESP5_TXD0: J105.4, U604.37 (TXD0)
/PROG_ESP6_EN: J106.2, U704.3 (EN)
/PROG_ESP6_IO0: J106.3, U704.27 (IO0)
/PROG_ESP6_PWR: C701.1, J106.1, U701.6 (VIN2)
/PROG_ESP6_RXD0: J106.5, U704.36 (RXD0)
/PROG_ESP6_TXD0: J106.4, U704.37 (TXD0)
/PROG_ESP7_EN: J107.2, U804.3 (EN)
/PROG_ESP7_IO0: J107.3, U804.27 (IO0)
/PROG_ESP7_PWR: C801.1, J107.1, U801.6 (VIN2)
/PROG_ESP7_RXD0: J107.5, U804.36 (RXD0)
/PROG_ESP7_TXD0: J107.4, U804.37 (TXD0)
/PROG_ESP8_EN: J108.2, U904.3 (EN)
/PROG_ESP8_IO0: J108.3, U904.27 (IO0)
/PROG_ESP8_PWR: C901.1, J108.1, U901.6 (VIN2)
/PROG_ESP8_RXD0: J108.5, U904.36 (RXD0)
/PROG_ESP8_TXD0: J108.4, U904.37 (TXD0)
/PROG_ESP9_EN: J109.2, U1004.3 (EN)
/PROG_ESP9_IO0: J109.3, U1004.27 (IO0)
/PROG_ESP9_PWR: C1001.1, J109.1, U1001.6 (VIN2)
/PROG_ESP9_RXD0: J109.5, U1004.36 (RXD0)
/PROG_ESP9_TXD0: J109.4, U1004.37 (TXD0)
/RS485_A: R101.2, R102.1, U208.6 (A), U308.6 (A), U408.6 (A), U508.6 (A), U608.6 (A), U708.6 (A), U808.6 (A), U908.6 (A), U1008.6 (A), U1103.6 (A)
/SAMD21/BACKLIGHT_PWM: J1102.3, U206.4 (CTRL), U306.4 (CTRL), U406.4 (CTRL), U506.4 (CTRL), U606.4 (CTRL), U706.4 (CTRL), U806.4 (CTRL), U906.4 (CTRL), U1006.4 (CTRL), U1104.6 (SCL)
/SAMD21/PWR_IN: C1102.1, U1102.3 (VI)
/SAMD21/SAMD21_3V3: C1101.1, C1105.1, C1106.1, D1102.2 (A), J1104.4 (VDD), RN1101.1 (4), RN1101.2, RN1101.3, RN1101.4, U1101.14 (VCC), U1103.8 (VCC), U1104.12 (3V)
/SAMD21/SAMD21_5V: C1103.1, C1104.1, D1101.2 (A), J1101.1, J1102.1, J1103.1, U1102.2 (VO), U1104.14 (5V)
/SAMD21/SAMD_MISO: J1101.3, U1101.3 (B1), U1104.10 (MI)
/SAMD21/SAMD_MOSI: J1101.4, U1101.5 (A2), U1104.11 (MO)
/SAMD21/SAMD_SCK: J1101.2, U1101.9 (A3), U1104.9 (SCK)
/SAMD21/SAMD_SDA: J1102.2, U1104.5 (SDA)
/SAMD21/SPI_MISO_µSD: J1104.7 (DAT0), RN1101.7 (5), U205.2 (A1), U305.2 (A1), U405.2 (A1), U505.2 (A1), U605.2 (A1), U705.2 (A1), U805.2 (A1), U905.2 (A1), U1005.2 (A1), U1101.2 (A1)
/SAMD21/SPI_MOSI_µSD: J1104.3 (CMD), RN1101.6, U205.6 (B2), U305.6 (B2), U405.6 (B2), U505.6 (B2), U605.6 (B2), U705.6 (B2), U805.6 (B2), U905.6 (B2), U1005.6 (B2), U1101.6 (B2)
/SAMD21/SPI_SCK_µSD: J1104.5 (CLK), RN1101.8, U205.8 (B3), U305.8 (B3), U405.8 (B3), U505.8 (B3), U605.8 (B3), U705.8 (B3), U805.8 (B3), U905.8 (B3), U1005.8 (B3), U1101.8 (B3)
/SAMD21/SPI_µSD_BUS_CONNECT: J1103.2, U1101.1 (1~OE), U1101.4 (2~OE), U1101.10 (3~OE), U1101.13 (4~OE), U1104.1 (A0)
/SAMD21/UART-RS485_RX: J1102.5, U1103.1 (RO), U1104.8 (RX)
/SAMD21/UART-RS485_TX: J1102.4, U1103.4 (DI), U1104.7 (TX)
/SAMD21/UART_RS485_DE: J1103.5, U1103.2 (~RE), U1103.3 (DE), U1104.4 (A3)
GND: C201.2, C202.2, C203.2, C204.2, C205.2, C206.2, C207.2, C208.2, C209.2, C210.2, C211.2, C212.2, C213.2, C214.2, C215.2, C216.2, C301.2, C302.2, C303.2, C304.2, C305.2, C306.2, C307.2, C308.2, C309.2, C310.2, C311.2, C312.2, C313.2, C314.2, C315.2, C316.2, C401.2, C402.2, C403.2, C404.2, C405.2, C406.2, C407.2, C408.2, C409.2, C410.2, C411.2, C412.2, C413.2, C414.2, C415.2, C416.2, C501.2, C502.2, C503.2, C504.2, C505.2, C506.2, C507.2, C508.2, C509.2, C510.2, C511.2, C512.2, C513.2, C514.2, C515.2, C516.2, C601.2, C602.2, C603.2, C604.2, C605.2, C606.2, C607.2, C608.2, C609.2, C610.2, C611.2, C612.2, C613.2, C614.2, C615.2, C616.2, C701.2, C702.2, C703.2, C704.2, C705.2, C706.2, C707.2, C708.2, C709.2, C710.2, C711.2, C712.2, C713.2, C714.2, C715.2, C716.2, C801.2, C802.2, C803.2, C804.2, C805.2, C806.2, C807.2, C808.2, C809.2, C810.2, C811.2, C812.2, C813.2, C814.2, C815.2, C816.2, C901.2, C902.2, C903.2, C904.2, C905.2, C906.2, C907.2, C908.2, C909.2, C910.2, C911.2, C912.2, C913.2, C914.2, C915.2, C916.2, C1001.2, C1002.2, C1003.2, C1004.2, C1005.2, C1006.2, C1007.2, C1008.2, C1009.2, C1010.2, C1011.2, C1012.2, C1013.2, C1014.2, C1015.2, C1016.2, C1101.2, C1102.2, C1103.2, C1104.2, C1105.2, C1106.2, J101.6, J102.6, J103.6, J104.6, J105.6, J106.6, J107.6, J108.6, J109.6, J201.4 (GND), J201.34 (GND), J201.40 (GND), J201.S1 (M), J201.S2 (M), J301.4 (GND), J301.34 (GND), J301.40 (GND), J301.S1 (M), J301.S2 (M), J401.4 (GND), J401.34 (GND), J401.40 (GND), J401.S1 (M), J401.S2 (M), J501.4 (GND), J501.34 (GND), J501.40 (GND), J501.S1 (M), J501.S2 (M), J601.4 (GND), J601.34 (GND), J601.40 (GND), J601.S1 (M), J601.S2 (M), J701.4 (GND), J701.34 (GND), J701.40 (GND), J701.S1 (M), J701.S2 (M), J801.4 (GND), J801.34 (GND), J801.40 (GND), J801.S1 (M), J801.S2 (M), J901.4 (GND), J901.34 (GND), J901.40 (GND), J901.S1 (M), J901.S2 (M), J1001.4 (GND), J1001.34 (GND), J1001.40 (GND), J1001.S1 (M), J1001.S2 (M), J1101.5, J1102.6, J1103.6, J1104.6 (VSS), J1104.9 (SHIELD), R201.2, R202.2, R301.2, R302.2, R401.2, R402.2, R501.2, R502.2, R601.2, R602.2, R701.2, R702.2, R801.2, R802.2, R901.2, R902.2, R1001.2, R1002.2, R1101.2, R1102.2, RN202.5, RN202.6, RN202.7 (5), RN202.8, RN302.5, RN302.6, RN302.7 (5), RN302.8, RN402.5, RN402.6, RN402.7 (5), RN402.8, RN502.5, RN502.6, RN502.7 (5), RN502.8, RN602.5, RN602.6, RN602.7 (5), RN602.8, RN702.5, RN702.6, RN702.7 (5), RN702.8, RN802.5, RN802.6, RN802.7 (5), RN802.8, RN902.5, RN902.6, RN902.7 (5), RN902.8, RN1002.5, RN1002.6, RN1002.7 (5), RN1002.8, U201.1 (GND), U201.4 (~ON), U201.5 (GND), U202.3 (GND), U202.7 (GND), U203.4 (GND), U204.1 (GND), U204.40 (GND), U204.41 (GND), U205.7 (GND), U206.2 (GND), U208.5 (GND), U301.1 (GND), U301.4 (~ON), U301.5 (GND), U302.3 (GND), U302.7 (GND), U303.4 (GND), U304.1 (GND), U304.40 (GND), U304.41 (GND), U305.7 (GND), U306.2 (GND), U308.5 (GND), U401.1 (GND), U401.4 (~ON), U401.5 (GND), U402.3 (GND), U402.7 (GND), U403.4 (GND), U404.1 (GND), U404.40 (GND), U404.41 (GND), U405.7 (GND), U406.2 (GND), U408.5 (GND), U501.1 (GND), U501.4 (~ON), U501.5 (GND), U502.3 (GND), U502.7 (GND), U503.4 (GND), U504.1 (GND), U504.40 (GND), U504.41 (GND), U505.7 (GND), U506.2 (GND), U508.5 (GND), U601.1 (GND), U601.4 (~ON), U601.5 (GND), U602.3 (GND), U602.7 (GND), U603.4 (GND), U604.1 (GND), U604.40 (GND), U604.41 (GND), U605.7 (GND), U606.2 (GND), U608.5 (GND), U701.1 (GND), U701.4 (~ON), U701.5 (GND), U702.3 (GND), U702.7 (GND), U703.4 (GND), U704.1 (GND), U704.40 (GND), U704.41 (GND), U705.7 (GND), U706.2 (GND), U708.5 (GND), U801.1 (GND), U801.4 (~ON), U801.5 (GND), U802.3 (GND), U802.7 (GND), U803.4 (GND), U804.1 (GND), U804.40 (GND), U804.41 (GND), U805.7 (GND), U806.2 (GND), U808.5 (GND), U901.1 (GND), U901.4 (~ON), U901.5 (GND), U902.3 (GND), U902.7 (GND), U903.4 (GND), U904.1 (GND), U904.40 (GND), U904.41 (GND), U905.7 (GND), U906.2 (GND), U908.5 (GND), U1001.1 (GND), U1001.4 (~ON), U1001.5 (GND), U1002.3 (GND), U1002.7 (GND), U1003.4 (GND), U1004.1 (GND), U1004.40 (GND), U1004.41 (GND), U1005.7 (GND), U1006.2 (GND), U1008.5 (GND), U1101.7 (GND), U1102.1 (GND), U1103.5 (GND), U1104.13 (GND)
unnamed: D201.1 (K), R201.1
unnamed: D202.1 (K), RN202.1 (4)
unnamed: D203.1 (K), RN202.2
unnamed: D204.1 (K), RN202.3
unnamed: D205.1 (K), RN202.4
unnamed: D301.1 (K), R301.1
unnamed: D302.1 (K), RN302.1 (4)
unnamed: D303.1 (K), RN302.2
unnamed: D304.1 (K), RN302.3
unnamed: D305.1 (K), RN302.4
unnamed: D401.1 (K), R401.1
unnamed: D402.1 (K), RN402.1 (4)
unnamed: D403.1 (K), RN402.2
unnamed: D404.1 (K), RN402.3
unnamed: D405.1 (K), RN402.4
unnamed: D501.1 (K), R501.1
unnamed: D502.1 (K), RN502.1 (4)
unnamed: D503.1 (K), RN502.2
unnamed: D504.1 (K), RN502.3
unnamed: D505.1 (K), RN502.4
unnamed: D601.1 (K), R601.1
unnamed: D602.1 (K), RN602.1 (4)
unnamed: D603.1 (K), RN602.2
unnamed: D604.1 (K), RN602.3
unnamed: D605.1 (K), RN602.4
unnamed: D701.1 (K), R701.1
unnamed: D702.1 (K), RN702.1 (4)
unnamed: D703.1 (K), RN702.2
unnamed: D704.1 (K), RN702.3
unnamed: D705.1 (K), RN702.4
unnamed: D801.1 (K), R801.1
unnamed: D802.1 (K), RN802.1 (4)
unnamed: D803.1 (K), RN802.2
unnamed: D804.1 (K), RN802.3
unnamed: D805.1 (K), RN802.4
unnamed: D901.1 (K), R901.1
unnamed: D902.1 (K), RN902.1 (4)
unnamed: D903.1 (K), RN902.2
unnamed: D904.1 (K), RN902.3
unnamed: D905.1 (K), RN902.4
unnamed: D1001.1 (K), R1001.1
unnamed: D1002.1 (K), RN1002.1 (4)
unnamed: D1003.1 (K), RN1002.2
unnamed: D1004.1 (K), RN1002.3
unnamed: D1005.1 (K), RN1002.4
unnamed: D1101.1 (K), R1101.1
unnamed: D1102.1 (K), R1102.1
unnamed: C213.1, C215.1, J201.1 (LEDA), U206.5 (V_{OUT})
unnamed: C313.1, C315.1, J301.1 (LEDA), U306.5 (V_{OUT})
unnamed: C413.1, C415.1, J401.1 (LEDA), U406.5 (V_{OUT})
unnamed: C513.1, C515.1, J501.1 (LEDA), U506.5 (V_{OUT})
unnamed: C613.1, C615.1, J601.1 (LEDA), U606.5 (V_{OUT})
unnamed: C713.1, C715.1, J701.1 (LEDA), U706.5 (V_{OUT})
unnamed: C813.1, C815.1, J801.1 (LEDA), U806.5 (V_{OUT})
unnamed: C913.1, C915.1, J901.1 (LEDA), U906.5 (V_{OUT})
unnamed: C1013.1, C1015.1, J1001.1 (LEDA), U1006.5 (V_{OUT})
unnamed: J201.2 (LEDK), J201.3 (LEDK), R202.1, U206.3 (FB)
unnamed: C212.1, C214.1, L201.2, U206.6 (V_{IN})
unnamed: J301.2 (LEDK), J301.3 (LEDK), R302.1, U306.3 (FB)
unnamed: C312.1, C314.1, L301.2, U306.6 (V_{IN})
unnamed: J401.2 (LEDK), J401.3 (LEDK), R402.1, U406.3 (FB)
unnamed: C412.1, C414.1, L401.2, U406.6 (V_{IN})
unnamed: J501.2 (LEDK), J501.3 (LEDK), R502.1, U506.3 (FB)
unnamed: C512.1, C514.1, L501.2, U506.6 (V_{IN})
unnamed: J601.2 (LEDK), J601.3 (LEDK), R602.1, U606.3 (FB)
unnamed: C612.1, C614.1, L601.2, U606.6 (V_{IN})
unnamed: J701.2 (LEDK), J701.3 (LEDK), R702.1, U706.3 (FB)
unnamed: C712.1, C714.1, L701.2, U706.6 (V_{IN})
unnamed: J801.2 (LEDK), J801.3 (LEDK), R802.1, U806.3 (FB)
unnamed: C812.1, C814.1, L801.2, U806.6 (V_{IN})
unnamed: J901.2 (LEDK), J901.3 (LEDK), R902.1, U906.3 (FB)
unnamed: C912.1, C914.1, L901.2, U906.6 (V_{IN})
unnamed: J1001.2 (LEDK), J1001.3 (LEDK), R1002.1, U1006.3 (FB)
unnamed: C1012.1, C1014.1, L1001.2, U1006.6 (V_{IN})

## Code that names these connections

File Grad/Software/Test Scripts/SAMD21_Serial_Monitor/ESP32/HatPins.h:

#pragma once
#include <Arduino.h>  // provides pinMode(), digitalWrite(), HIGH/LOW, etc.

/* =======================
   ESP32 Display Board Pins
   ======================= */

#define PIN_FRAME_SYNC_IN   1   /* IO01 */

/* LCD RGB data bus */
#define PIN_LCD_DB0   2
#define PIN_LCD_DB1   4
#define PIN_LCD_DB2   5
#define PIN_LCD_DB3   6
#define PIN_LCD_DB4   7
#define PIN_LCD_DB5   13
#define PIN_LCD_DB6   14
#define PIN_LCD_DB7   15
#define PIN_LCD_DB8   16
#define PIN_LCD_DB9   17
#define PIN_LCD_DB10  18
#define PIN_LCD_DB11  19
#define PIN_LCD_DB12  20
#define PIN_LCD_DB13  42
#define PIN_LCD_DB14  47
#define PIN_LCD_DB15  48

/* LCD control/timing */
#define PIN_LCD_PCLK   38
#define PIN_LCD_DE     39
#define PIN_LCD_VSYNC  40
#define PIN_LCD_HSYNC  41

/* SPI bus */
#define PIN_SPI_MOSI   8
#define PIN_SPI_SCK    9

/* Strapping pins (use after boot) */
#define PIN_SPI_MISO   45  /* IO45 strap */
#define PIN_SPI_CS0    46  /* IO46 strap -> decoder A input */

/* Decoder B input */
#define PIN_SPI_CS1    10  /* IO10 -> decoder B input */

/* Reserved for PSRAM (don’t touch) */
#define PIN_PSRAM_0    35
#define PIN_PSRAM_1    36
#define PIN_PSRAM_2    37

/* Strap pin unused */
#define PIN_STRAP_3_UNUSED  3

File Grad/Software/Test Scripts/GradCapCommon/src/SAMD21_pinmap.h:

/*
 * File: SAMD21_pinmap.h
 * Description: Pin map for the SAMD21 companion microcontroller board. Defines SPI, RS-485, button, frame-sync, microSD control, and NeoPixel connections.
 * Function count: 0 functions; pin definitions only
 * Target microcontroller: SAMD21
 */

#pragma once

/* Pin map only: this file contains SAMD21 board-level GPIO assignments and does not declare callable functions. */

#ifdef __cplusplus
extern "C" {
#endif

#define SAMD_MOSI             (A10)  /* PA10 */
#define SAMD_MISO             (A9)   /* PA09 */
#define SAMD_SCK              (A8)   /* PA11 */

#define SAMD_RS485_RX_PIN     (A7)   /* PA07 */
#define SAMD_RS485_TX_PIN     (A6)   /* PA06 */

#define BACKLIGHT_PWM_OUT     (5)    /* PA17 */
#define SAMD_RS485_DE_PIN     (4)    /* PA16  (QT Py labeled SDA) */

#define BUTTON_SENSE          (A3)   /* PA05 */
#define FRAME_SYNC_OUT        (A2)   /* PA04 */
#define SAMD_CS_uSD           (A1)   /* PA03 */
#define SAMD_uSD_BUS_CONNECT  (A0)   /* PA02 */

#define NEOPIXEL_DATA         (11)   /* PA18 */
#define NEOPIXEL_POWER        (12)   /* PA15 */

#ifdef __cplusplus
}
#endif

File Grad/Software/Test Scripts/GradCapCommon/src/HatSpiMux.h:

/*
 * File: HatSpiMux.h
 * Description: C-style interface for the SPI target multiplexer that selects the flash, SD card, LCD sideband, or a disconnected idle state on the shared SPI bus.
 * Function count: 2 public API functions, 4 inline convenience helpers, and 1 enum
 * Target microcontroller: ESP32
 */

#pragma once
#include <Arduino.h>
#include "HatPins.h"

#ifdef __cplusplus
extern "C" {
#endif

/*
  SN74LVC1G139 mapping (per your datasheet wording):

    Inputs:
      A = ESP_CS0 = PIN_SPI_CS0  (strap pin IO46)
      B = ESP_CS1 = PIN_SPI_CS1

    Outputs:
      Y0 -> ESP_CS_FLASH (active-low)
      Y1 -> ESP_uSD_BUS_CONNECT (active-low)
      Y2 -> ESP_CS_uSD (active-low) [HARDWARE MOD: disconnected]
      Y3 -> ESP_CS_LCD  (active-low)

  HARDWARE MOD:
    - Y2 is physically disconnected
    - Y1 is tied to BOTH uSD_BUS_CONNECT and uSD_CS
    - Therefore: selecting Y1 asserts BOTH connect+CS low.

  We use the now-unused Y2 state (B=1, A=0) as "DISCONNECT".
  Decoder selection truth table (active-low one-hot):
    B A:
    0 0 -> Y0 (FLASH)
    0 1 -> Y1 (SD connect + SD CS)
    1 0 -> Y2 (DISCONNECT / unused)
    1 1 -> Y3 (LCD)
*/

typedef enum {
  SPI_TARGET_FLASH = 0,
  SPI_TARGET_SD    = 1,
  SPI_TARGET_DISCONNECT = 2,
  SPI_TARGET_LCD   = 3
} spi_target_t;

/* Call once in setup(), after boot */
/* Initialize the SPI target multiplexer after boot and drive it to a safe disconnected idle state.
   Input: None.
   Output: None. */
void hat_spi_mux_begin(void);

/* Select one of the four states above */
/* Select which SPI target is connected to the shared bus.
   Input: Desired SPI target enum value.
   Output: None. */
void hat_spi_mux_select(spi_target_t target);

/* Convenience helpers */
/* Convenience helper that connects the external flash chip to the shared SPI bus.
   Input: None.
   Output: None. */
static inline void hat_spi_mux_select_flash(void) { hat_spi_mux_select(SPI_TARGET_FLASH); }
/* Convenience helper that connects the microSD path to the shared SPI bus.
   Input: None.
   Output: None. */
static inline void hat_spi_mux_select_sd(void)    { hat_spi_mux_select(SPI_TARGET_SD); }
/* Convenience helper that disconnects all active SPI peripherals from the shared bus.
   Input: None.
   Output: None. */
static inline void hat_spi_mux_disconnect(void)   { hat_spi_mux_select(SPI_TARGET_DISCONNECT); }
/* Convenience helper that connects the LCD serial sideband interface to the shared SPI bus.
   Input: None.
   Output: None. */
static inline void hat_spi_mux_select_lcd(void)   { hat_spi_mux_select(SPI_TARGET_LCD); }

#ifdef __cplusplus
} // extern "C"
#endif

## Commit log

2024-10-14 Generated a few had designs
2024-10-14 Finished PCB layout
2024-10-14 Fixed silkscreen text
2024-10-15 Generated Gerber files, ordered
2024-12-13 Programmed hat modes
    Mode 1) Starry Night (~100 mA)
    Mode 2) Party Mode 1 (~1280 mA)
    Mode 3) KI5SXY Callsign (~200-400 mA)
    Mode 4) Party Mode 2 (~500-800 mA)
2025-07-29 Added image of schematic
2026-02-13 Beginnings of cap V2
2026-02-15 Schematic feels done now
2026-02-15 Fix to SD Card Symbol
2026-02-15 Start of modular PCB
2026-02-15 Prototype of PCB layout
2026-02-15 Fixed flipped FPC connector pinout
2026-02-15 Added components, more layout testing
2026-02-16 More routing progress
2026-02-16 Small tweaks
2026-02-20 Rev A gerbers generated, sent to fab
2026-02-28 Reorganized repo by project
2026-03-18 Software test scripts created for PCB checkout
2026-03-22 Reorganized file structure
2026-03-22 Created working flash test program, upgraded flash library
2026-03-23 Added SD card read/write test
2026-03-23 Corrected bus disconnect switch datasheet link
2026-03-23 Rewrote SAMD21 RS485 bridge to c++
2026-03-23 Created RS485 bus abstraction layer
    This helps get around the limitations of the bus being half-duplex.
    This also allows the SAMD21 to communicate with each ESP32 separately, while also addressing each ESP as they have traffic to send
    This is grow into how we control access to the micro SD card among every ESP
2026-04-13 LCDImageTest3 displays an image
    Had to make some hardware tweaks to pull this off. GPIO43 and GPIO44 needed to be jumpered to DB16 and DB17, and GPIO3 needed to be jumpered to RST on the LCD.
    GPIO 3 was left open because it was a strapping pin, but it turns out that doesn't matter here since the LCD gets reset after boot through this pin anyway.
    GPIO43/44 are used for the UART0 bootloading, but again this only is a problem during program loading and not during runtime. Jumpering these to DB16 add DB17 takes a steady hand...
    My original intention was to run the LCD display in RGB565 16-bit color mode since the ST7701 can operate in this mode. According to Table 12 of the ST7701 datasheet,
2026-04-20 Added comments to library files
2026-04-22 Reorganized software test scripts
2026-04-22 Developed bus protocol test script
2026-04-22 Added required library files to test scripts
